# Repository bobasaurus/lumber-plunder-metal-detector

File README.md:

A VLF induction balance metal detector with a wooden body.  Previously built with an android smartphone, currently switching to a STM32 Nucleo module and OLED display on a custom PCB.  

This project is influenced by and tries to improve upon similar DIY metal detectors, including the following:
* Neco Smart Hunter EN:  https://neco-desarrollo.es/smart-hunter
* The vistac2000 pc-based metal detector with usb interface: https://www.geotech1.com/forums/showthread.php?14102-Let-s-made-a-PC-base-metal-detector-with-usb-interface-!!!
* The TGSL (for the coil design): https://www.geotech1.com/forums/showthread.php?15710-TGSL-Complete-Details
* More TGSL info: https://simplemetaldetector.com/induction-balance-metal-detectors/tesoro-golden-sabre-light-tlsl/

The first version of the schematic is available here:

https://github.com/bobasaurus/lumber-plunder-metal-detector/blob/main/images/lumber%20plunder%20metal%20detector%20schematic%20v1.pdf

I followed the coil design and wrapping guides for the TGSL linked above, though using a thicker magnet wire I happened to have on hand (and using fewer wraps to reduce weight):

After wrapping, the coils were stiffened with dental floss knots and some waterlox wood finish.  They were then shielded by wrapping sparsely with bare copper wire then coated with a mixture of polyurethane and graphite powder.  Finally, the coils were wrapped in electrical tape to insulate.  

After determining the correct amount of overlap to cancel out the transmit signal on the receive coil, I designed and built a wooden case for the coils with dowel adjusters to keep the receive coil nulled while the epoxy cured (measured with an oscilloscope while transmitting a 15 kHz sine wave on the tx coil):

I'm using a shielded USB cable to connect the coils to the control circuitry.  Then a smartphone app generates the transmit signal and receives the return signal using the 3.5 mm audio jack.  

2022/2/10:  I found a problem with the schematic, I needed to put a 4.7k resistor from the microphone input to ground in order for my phone to detect it as a "headset" and change the audio input device from the internal mic to the cable/plug.  I'll update it soon.  

2022/11/25:  This detector has major issues with ground balance, redesigning with a V2 schematic now to try and fix this.  Will likely change to using an stm32 nucleo board w/ an OLED instead of using a smartphone.

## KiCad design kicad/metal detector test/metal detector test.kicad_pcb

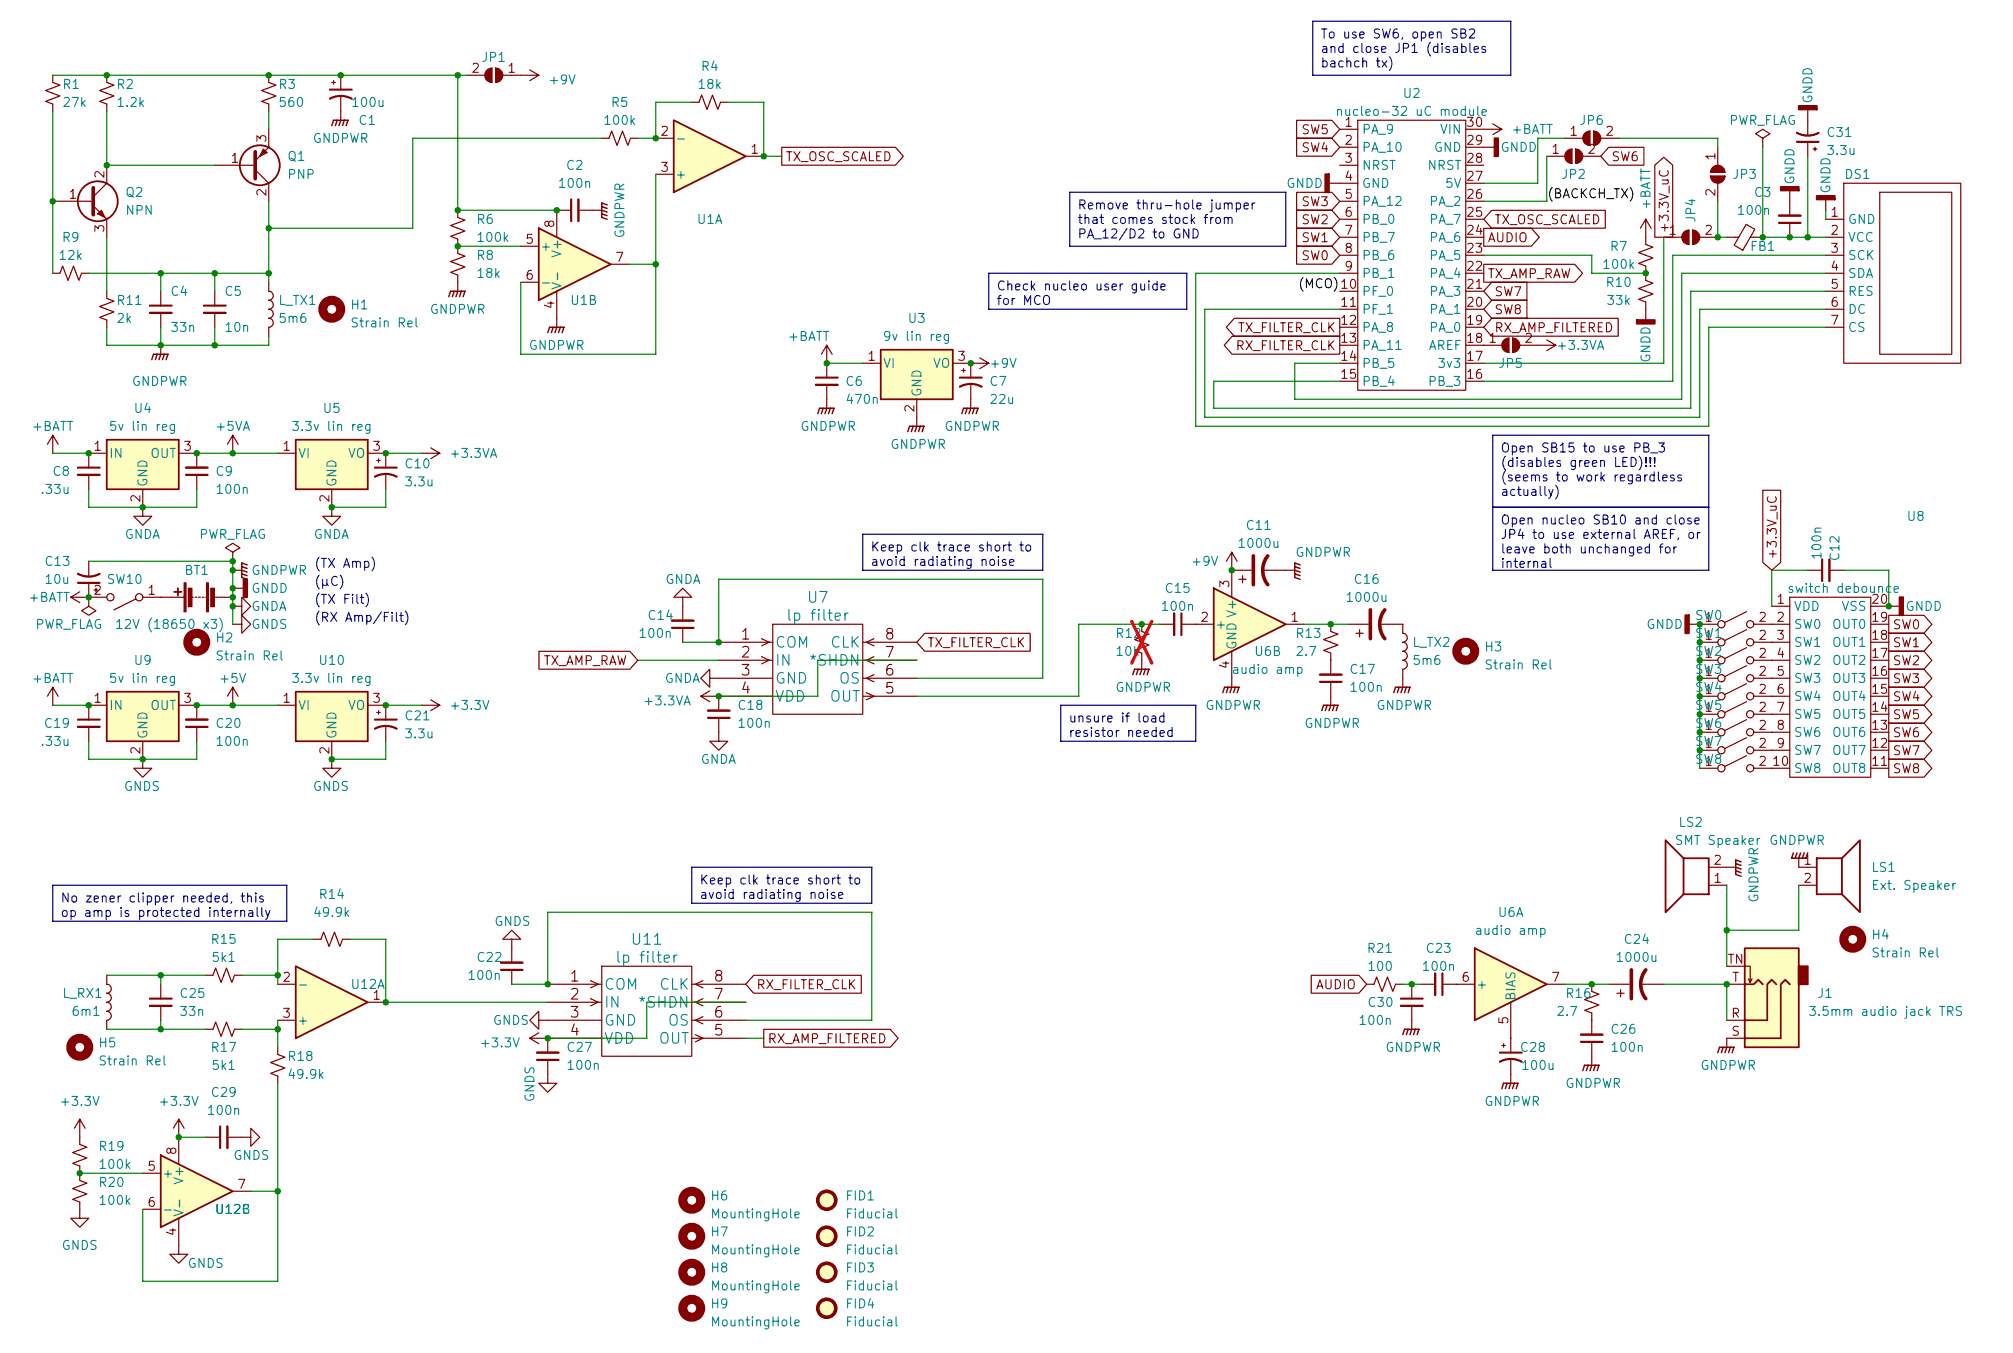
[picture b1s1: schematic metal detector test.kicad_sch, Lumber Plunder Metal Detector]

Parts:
BT1: 12V (18650 x3); PinHeader_1x02_P2.54mm_Vertical; MPN 106990288
C1, C28: 100u; C_Polarized_1206_3216Metric_HandSolder_allen
C2, C3, C9, C12, C14, C15, C17, C18, C20, C22, C23, C26, C27, C29, C30: 100n; C_0805_2012Metric_Pad1.18x1.45mm_HandSolder
C4, C25: 33n; C_0805_2012Metric_Pad1.18x1.45mm_HandSolder
C5: 10n; C_0805_2012Metric_Pad1.18x1.45mm_HandSolder
C6: 470n; C_1206_3216Metric_Pad1.33x1.80mm_HandSolder
C7: 22u; C_Polarized_1206_3216Metric_HandSolder_allen
C8, C19: .33u; C_0805_2012Metric_Pad1.18x1.45mm_HandSolder
C10, C21, C31: 3.3u; C_Polarized_0805_2012Metric_HandSolder_allen
C11, C16, C24: 1000u; CP_Radial_D10.0mm_P5.00mm; MPN A750MV108M1EAAE014
C13: 10u; C_Polarized_1206_3216Metric_HandSolder_allen
DS1: 2.42_inch_128x64_oled; oled_2.42in_128x64; MPN B09LND6QJ1
FB1: ferrite bead smt; L_0805_2012Metric_Pad1.05x1.20mm_HandSolder; MPN HZ0805E601R-10
FID1, FID2, FID3, FID4: Fiducial; Fiducial_0.5mm_Mask1.5mm
H1, H2, H3, H4, H5: Strain Rel; mounting_hole_3mm
H6, H7, H8, H9: MountingHole; mounting_hole_4-40_thru
J1: 3.5mm audio jack TRS; SJ-3524-SMT_audio_jack_with_tip_switch_smt; MPN SJ-3524-SMT
JP1: SolderJumper_2_Open_big; SolderJumper-2_Open_big_allen
JP2, JP3, JP4, JP5, JP6: SolderJumper_2_Open; SolderJumper-2_P1.3mm_Open_Pad1.0x1.5mm
LS1: Ext. Speaker; PinHeader_1x02_P2.54mm_Vertical
LS2: SMT Speaker; CDS-13138-SMT-TR_speaker_smt; MPN CDS-13138-SMT-TR
L_RX1: 6m1; PinHeader_1x02_P2.54mm_Vertical
L_TX1, L_TX2: 5m6; PinHeader_1x02_P2.54mm_Vertical
Q1: PNP; SOT-89-3_Handsoldering_allen; MPN 2SA2071T100Q
Q2: NPN; SOT-89-3_Handsoldering_allen; MPN 2SC5824T100Q
R1: 27k; R_0805_2012Metric_Pad1.20x1.40mm_HandSolder
R2: 1.2k; R_0805_2012Metric_Pad1.20x1.40mm_HandSolder
R3: 560; R_0805_2012Metric_Pad1.20x1.40mm_HandSolder
R4, R8: 18k; R_0805_2012Metric_Pad1.20x1.40mm_HandSolder
R5, R6, R7, R19, R20: 100k; R_0805_2012Metric_Pad1.20x1.40mm_HandSolder
R9: 12k; R_0805_2012Metric_Pad1.20x1.40mm_HandSolder
R10: 33k; R_0805_2012Metric_Pad1.20x1.40mm_HandSolder
R11: 2k; R_0805_2012Metric_Pad1.20x1.40mm_HandSolder
R12: 10k; R_0805_2012Metric_Pad1.20x1.40mm_HandSolder; not fitted
R13, R16: 2.7; R_0805_2012Metric_Pad1.20x1.40mm_HandSolder
R14, R18: 49.9k; R_0805_2012Metric_Pad1.20x1.40mm_HandSolder
R15, R17: 5k1; R_0805_2012Metric_Pad1.20x1.40mm_HandSolder
R21: 100; R_0805_2012Metric_Pad1.20x1.40mm_HandSolder
SW0, SW1, SW2, SW3, SW4, SW5, SW6, SW7, SW8: SW_SPST; SW_SPST_PTS647; MPN PTS 647 SN50 SMTR2 LFS
SW10: SW_SPST; A11AH_right_angle_toggle_switch; MPN A11AH
U1: op amp (higher voltage); SOIC-8_3.9x4.9mm_P1.27mm; MPN OPA2140AID
U2: nucleo-32 uC module; Nucleo-32_allen; MPN NUCLEO-F303K8
U3: 9v lin reg; SOT-223-3_TabPin2; MPN LM2940IMP-9.0/NOPB
U4, U9: 5v lin reg; SOT-223-3_TabPin2; MPN UA78M05CDCYRG3
U5, U10: 3.3v lin reg; SOT-223-3_TabPin2; MPN LT1129CST-3.3#PBF
U6: audio amp; TO-263-7_TabPin4; MPN LM4752TS
U7, U11: lp filter; TSSOP-8_4.4x3mm_P0.65mm; MPN MAX7423EUA+
U8: switch debounce; SOIC-20W_7.5x12.8mm_P1.27mm; MPN LS20-S
U12: op amp (lower voltage); SOIC-8_3.9x4.9mm_P1.27mm; MPN OPA2320AID

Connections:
+3.3V: C21.1, C27.2, C29.1, R19.1, U10.3 (VO), U11.4 (VDD), U11.7 (*SHDN), U12.8 (V+)
+3.3VA: C10.1, C18.2, JP5.2 (B), U5.3 (VO), U7.4 (VDD), U7.7 (*SHDN)
+3.3V_uC: C12.1, JP4.1 (A), U2.17 (3v3), U8.1 (VDD)
+5V: C20.2, U9.3 (OUT), U10.1 (VI)
+5VA: C9.2, U4.3 (OUT), U5.1 (VI)
+9V: C7.1, C11.1, JP1.1 (A), U3.3 (VO), U6.3 (V+)
+BATT: C6.1, C8.1, C13.1, C19.1, R7.1, SW10.2 (B), U2.30 (VIN), U3.1 (VI), U4.1 (IN), U9.1 (IN)
/(BACKCH_TX): JP2.1 (A), U2.26 (PA_2)
/(MCO): U2.10 (PF_0)
AUDIO: R21.1, U2.24 (PA_6)
GNDA: BT1.2 (-), C1.2, C2.2, C3.2, C4.2, C5.2, C6.2, C7.2, C8.2, C9.1, C10.2, C11.2, C12.2, C13.2, C14.2, C17.1, C18.1, C19.2, C20.1, C21.2, C22.2, C26.1, C27.1, C28.2, C29.2, C30.2, C31.2, DS1.1 (GND), J1.S, LS1.1, LS2.2, L_TX1.2, L_TX2.2, R8.2, R10.2, R11.2, R12.2, R20.2, SW0.1 (A), SW1.1 (A), SW2.1 (A), SW3.1 (A), SW4.1 (A), SW5.1 (A), SW6.1 (A), SW7.1 (A), SW8.1 (A), U1.4 (V-), U2.4 (GND), U2.29 (GND), U3.2 (GND), U4.2 (GND), U5.2 (GND), U6.4 (GND), U7.3 (GND), U8.20 (VSS), U9.2 (GND), U10.2 (GND), U11.3 (GND), U12.4 (V-)
unnamed: BT1.1 (+), SW10.1 (A)
unnamed: C16.1, R13.1, U6.1
unnamed: C16.2, L_TX2.1
unnamed: C17.2, R13.2
unnamed: C23.2, C30.1, R21.2
unnamed: C24.1, R16.1, U6.7
unnamed: C24.2, J1.R, J1.T
unnamed: C25.1, L_RX1.1, R15.1
unnamed: C25.2, L_RX1.2, R17.1
unnamed: C26.2, R16.2
unnamed: DS1.7 (CS), U2.9 (PB_1)
unnamed: DS1.6 (DC), U2.11 (PF_1)
unnamed: DS1.5 (RES), U2.15 (PB_4)
unnamed: DS1.3 (SCK), U2.16 (PB_3)
unnamed: DS1.4 (SDA), U2.14 (PB_5)
unnamed: C3.1, C31.1, DS1.2 (VCC), FB1.2
unnamed: J1.TN, LS1.2, LS2.1
unnamed: C1.1, C2.1, JP1.2 (B), R1.1, R2.1, R3.1, R6.1, U1.8 (V+)
unnamed: JP3.1 (A), JP6.2 (B)
unnamed: FB1.1, JP3.2 (B), JP4.2 (B)
unnamed: JP5.1 (A), U2.18 (AREF)
unnamed: JP6.1 (A), U2.27 (5V)
unnamed: Q1.1 (B), Q2.2 (C), R2.2
unnamed: C4.1, C5.1, L_TX1.1, Q1.2 (C), R5.1, R9.1
unnamed: Q1.3 (E), R3.2
unnamed: Q2.1 (B), R1.2, R9.2
unnamed: Q2.3 (E), R11.1
unnamed: SW0.2 (B), U8.2 (SW0)
unnamed: SW1.2 (B), U8.3 (SW1)
unnamed: SW2.2 (B), U8.4 (SW2)
unnamed: SW3.2 (B), U8.5 (SW3)
unnamed: SW4.2 (B), U8.6 (SW4)
unnamed: SW5.2 (B), U8.7 (SW5)
unnamed: SW6.2 (B), U8.8 (SW6)
unnamed: SW7.2 (B), U8.9 (SW7)
unnamed: SW8.2 (B), U8.10 (SW8)
unnamed: U1.3 (+), U1.6 (-), U1.7
unnamed: R4.1, R5.2, U1.2 (-)
unnamed: R6.2, R8.1, U1.5 (+)
unnamed: R7.2, R10.1, U2.23 (PA_5)
unnamed: C23.1, U6.6 (+)
unnamed: C28.1, U6.5 (BIAS)
unnamed: C15.1, U6.2 (+)
unnamed: C14.1, U7.1 (COM), U7.6 (OS)
unnamed: C15.2, R12.1, U7.5 (OUT)
unnamed: C22.1, U11.1 (COM), U11.6 (OS)
unnamed: R14.2, U11.2 (IN), U12.1
unnamed: R17.2, R18.1, U12.3 (+)
unnamed: R14.1, R15.2, U12.2 (-)
unnamed: R19.2, R20.1, U12.5 (+)
unnamed: R18.2, U12.6 (-), U12.7
RX_AMP_FILTERED: U2.19 (PA_0), U11.5 (OUT)
RX_FILTER_CLK: U2.13 (PA_11), U11.8 (CLK)
SW0: U2.8 (PB_6), U8.19 (OUT0)
SW1: U2.7 (PB_7), U8.18 (OUT1)
SW2: U2.6 (PB_0), U8.17 (OUT2)
SW3: U2.5 (PA_12), U8.16 (OUT3)
SW4: U2.2 (PA_10), U8.15 (OUT4)
SW5: U2.1 (PA_9), U8.14 (OUT5)
SW6: JP2.2 (B), U8.13 (OUT6)
SW7: U2.21 (PA_3), U8.12 (OUT7)
SW8: U2.20 (PA_1), U8.11 (OUT8)
TX_AMP_RAW: U2.22 (PA_4), U7.2 (IN)
TX_FILTER_CLK: U2.12 (PA_8), U7.8 (CLK)
TX_OSC_SCALED: R4.2, U1.1, U2.25 (PA_7)

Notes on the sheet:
Open nucleo SB10 and close JP4 to use external AREF, or leave both unchanged for internal
Remove thru-hole jumper that comes stock from PA_12/D2 to GND
No zener clipper needed, this op amp is protected internally
Keep clk trace short to avoid radiating noise
To use SW6, open SB2 and close JP1 (disables bachch tx)
Open SB15 to use PB_3 (disables green LED)!!! (seems to work regardless actually)
unsure if load resistor needed
Check nucleo user guide for MCO
(µC)
(TX Amp)
(TX Filt)
(RX Amp/Filt)

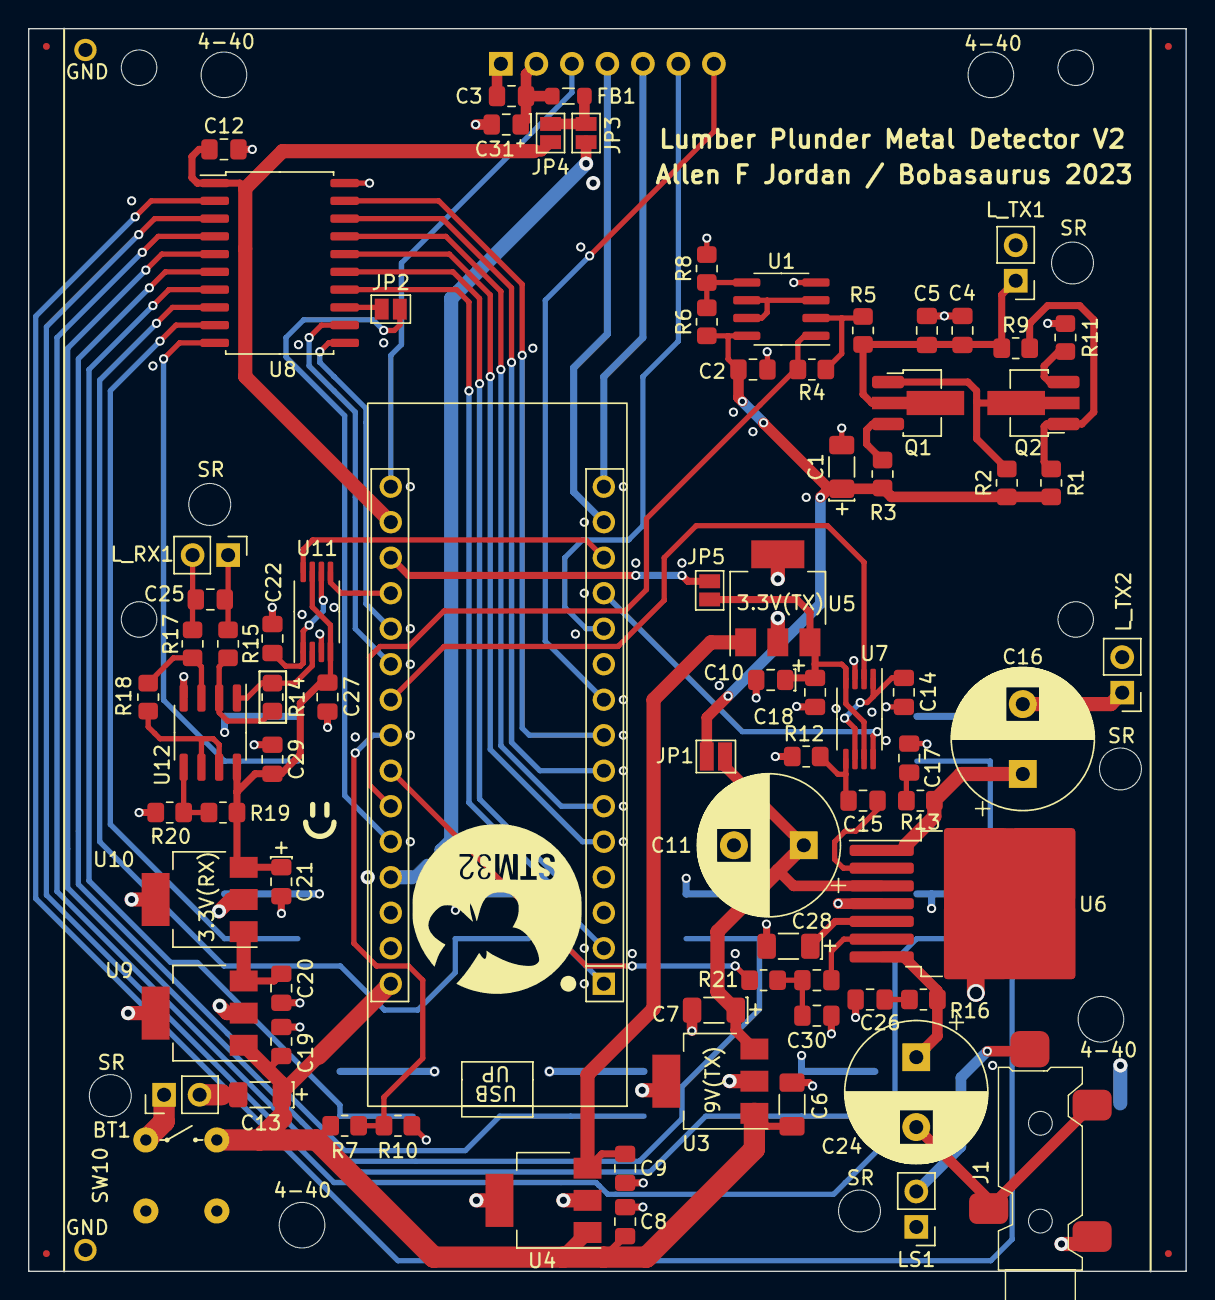
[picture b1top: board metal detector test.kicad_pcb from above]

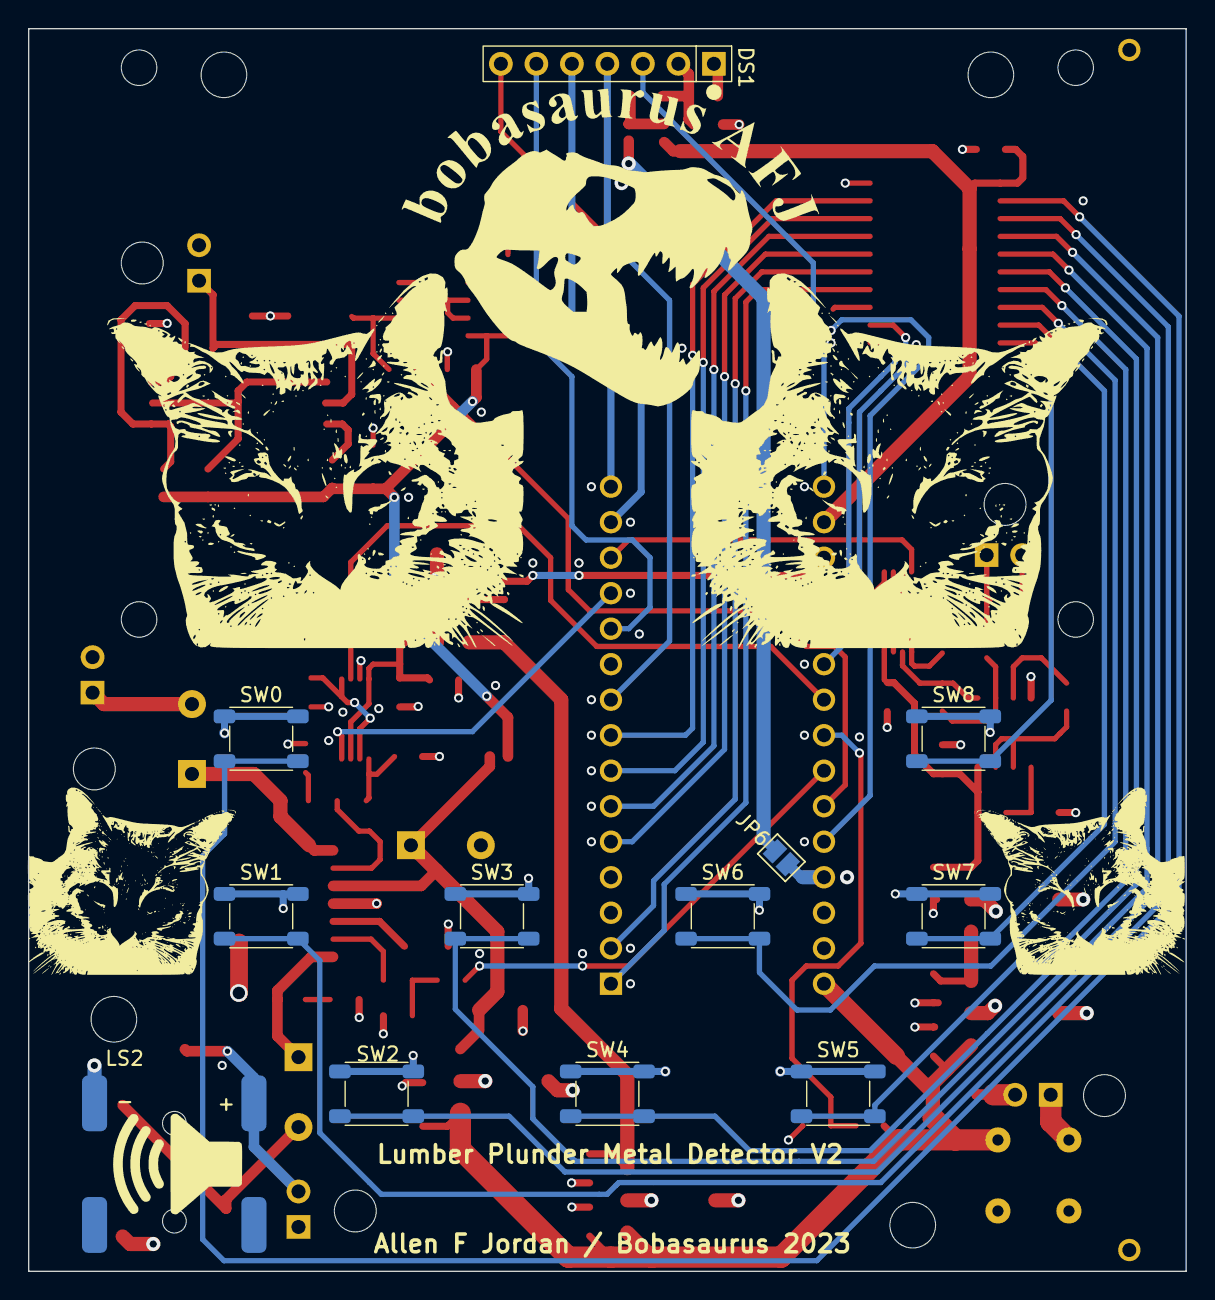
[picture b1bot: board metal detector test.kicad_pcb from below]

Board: 4 copper layers, 82.8 x 88.9 mm, 105 parts (13 on the bottom side), 75 nets.

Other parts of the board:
bobasaurus_logo: LOGO

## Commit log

2022-02-10 Initial summary of the project
2022-02-10 Initial commit of the app and images folder. The app is far from done, still figuring out graphing.
2022-02-10 Added some images and a schematic link
2022-02-10 Coil buildlng updates.
2022-02-10 More details.
2022-02-11 The app is basically working, need to tune the dlia
2022-02-12 Used the faster plot renderer, faster atan2 in dlia, and cleaned up plot appearance a bit.
2022-02-12 Fixed event handler renderer calls for pausing/resuming/etc
2022-02-15 Improved the digital lock-in amplifier and changed to using fast math library when possible
2022-02-22 working on improving audio latency, temporarily have phase graph disabled. May be a lag introduced on long run times currently that gets larger and larger, needs testing.
2022-03-06 Added a logo
2022-03-10 Lots of small changes to improve the recording
2022-11-26 Working on a pcb in kicad for V2 of this metal detector.
2022-11-26 Adding my symbol libraries
2022-11-26 updated readme with notes about V2
2022-11-26 Can't remember what I was doing here, hah. Moving away from the android project anyways.
2022-11-26 moving kicad libs
2022-11-26 Added TI's part library for their OPA2156IDR op amp
2022-11-26 moving lib dir
2022-11-26 Added ltspice simulation tests, also another part library for kicad
2022-11-27 Moved android app to the 'android' folder for better organization
2022-11-27 Added transistor footprints
2022-12-18 working on schematic
2023-03-13 Most major parts of the schematic are done, need to figure out uC connections including DAC.
2023-03-13 made the 9v regulator's caps 1206, may need to do the same to the 5v
2023-03-15 Connected nucleo uC module, mostly done
2023-03-19 Added clipper and switches, may need to move clipper behind resistors
2023-03-19 Realized the rx op amp has a built in limiter so no need for the external zeners, plus they apparently create a significant temperature-dependent offset voltage so that's not great.
2023-03-21 Added battery voltage measurement and a big cap on the battery input
2023-03-24 Added smt ferrite bead and cap to gnd on oled power input since amazon review reported that it's noise bleeds back into the uC, also made power for it optionally come from 5v or 3.3v with solder jump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
2023-03-24 Tweaks to make ERC pass, and redid designator anotations
2023-03-24 part num for ferrite
2023-03-24 Finished adding footprints, made MPN field for manufacturer part number and populated it for each part, figured out push button part and footprint
2023-03-25 Starting PCB layout. Also added alternate MPNs for a few more regulators sampled from TI
2023-03-27 Working on pcb layout, generated BOM
2023-03-30 slow progress
2023-03-31 Added holes on corners of OLED footprint after carefully measuring twice, working on layout still.
2023-03-31 Making custom mounting / strain relief holes
2023-04-01 making progress on pcb layout
2023-04-02 Mostly positioned the parts
2023-04-02 small changes
2023-04-04 Figuring out oled and battery holder placement
2023-04-06 most of the placement done
2023-04-08 working on part positions still
2023-04-09 Realized that I was accidentially using a pin required to use the external 8 MHz MCO xtal signal passed from the debugger chip, changed to another one.
2023-04-09 Adding a test stm32 project that tries out the peripherals I need on the nucleo-32 board along with the OLED display
2023-04-15 considering filtering the audio output
2023-04-17 Swapped DAC outputs for better impedance balancing
2023-10-02 experimenting with dac
2023-10-06 About halfway done routing tracks/traces
2023-10-07 Everything but gnd should be routed
2023-10-07 Finished routing I think, needs testing. Need to position designators as well.
2023-10-07 via stitching, designator placement
2023-10-08 Added a lot of fun silkscreen logos, and some other small tweaks
2023-10-08 Should be ready for fabrication
2023-10-08 Submitted for fabricaiton
2023-11-06 Figured out the complicated jumper / solder bridge settings, added a spreadsheet here with the results. The board won't work unless the jumpers are configured as in the spreadsheet.
2023-11-08 Basic tone generator test, and starting c++ template
2023-11-09 Rebuilt lumber plunder firmware project since I messed the first one's drivers up. This time I used my u8g2 example as a template so it imported all the right pins and clock/hw config.
2023-11-09 OLED is basically working
2023-11-09 converted to c++ structure
2023-11-09 Basic hardware tests are working so far: oled, backchannel uart tx, battery voltage measurement on ADC2, all switches (except #6 since it's disabled while using backchannel tx)
2023-11-09 Better monospaced font
2023-11-10 Battery voltage was reading low (ADC2), I noticed this on all ADC measurements on my earlier breadboard tests too. There is an ADC calibration available, but only when using the low level (LL) librar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
2023-11-10 experimenting with adc cal delays
2023-11-11 Experimenting with beeping
2023-12-28 Not sure what changed lol
2023-12-30 adding some wave generation test code from my laptop
2023-12-31 figuring out dma
2023-12-31 still working out dma details
2024-01-02 The latest cube mx version puts the generated code mostly in a separate source file: stm32f3xx_hal_msp.c. Turns out it can auto-generate the DMA code, and it was very similar to what I was working on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
2024-01-02 still working on dma, ugh
2024-02-05 added a test project for using the dma and dac to generate a wave. May be working, though I don't know what rate the timer is running at
2024-02-07 Updated gitignore for extra stm32cubeide workspace folder that's probably not needed
2024-03-09 Moving older experimental projects into the "old" directory
2024-03-12 finally got the dac + dma + timer working to make beeps on the speaker
2024-03-12 Able to change the amplitude and frequency with button presses (kind of crudely). For some reason it sounds like there are some duplicate tones at higher frequencies, maybe a bug in the wave calculat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
2024-03-12 Oops, the 8 MHz MCO clock from the ST-LINK loses power when USB is disconnected, killing the main uC. Switching back to internal oscillator (HSI) for now, will order a crystal and caps.
2024-03-13 reduced amplitude change step size to test amplifier output... it looks like the audio amp is clipping at about 6v peak-to-peak, annoyingly.
2024-03-15 I think I have the timer output compare working for generating 2 MHz squarewaves on the two output pins that need it (timer 1 channels 1 and 4 for the filter chips).
2024-03-17 adding my jupyter notebooks for metal detector testing
2024-03-17 simplified pulse generation in jupyter X R simulation
2024-03-18 Got the X R simulation working well, also have a better I Q version. In the final code will likely replace the second derivative with a high pass filter, or combine all the filters into a bandpass
2024-03-21 The 'hal_dac_dma_timer_tx_amp_raw' project now outputs sine waves on both DAC channels and outputs squarewave clocks to both filter chips
2024-03-24 added a note about the 9v regulator's capacitor... turns out it can increase as large as needed
2024-03-25 There was a bug in the sine wave generator that added artifical decimation/steps, fixed now. Also just outputting tx_amp_raw for now.
2024-04-05 current state of test code, it's giving a weird waveform shape though
2024-04-08 Added a new project that is a very basic dac test, going to make it output sine waves later
2024-04-09 Have basic delay-loop dac wave output working
2024-04-13 increased timer clock significantly to test higher dac sine wave output frequencies
2024-12-30 Small changes from latest stm32cubeide, plus changed sample rate and amplitude/center of dac basic testing project.
2024-12-30 adding a vs project to calculate the sine wave resolutions required to avoid missing dac steps
2024-12-31 Finally got a DMA/DAC example working. The "dac_dma" project is outputting a 10 kHz sine wave without any intervention from the main CPU. It turns out that a trigger is required, so I'm using Timer 6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
